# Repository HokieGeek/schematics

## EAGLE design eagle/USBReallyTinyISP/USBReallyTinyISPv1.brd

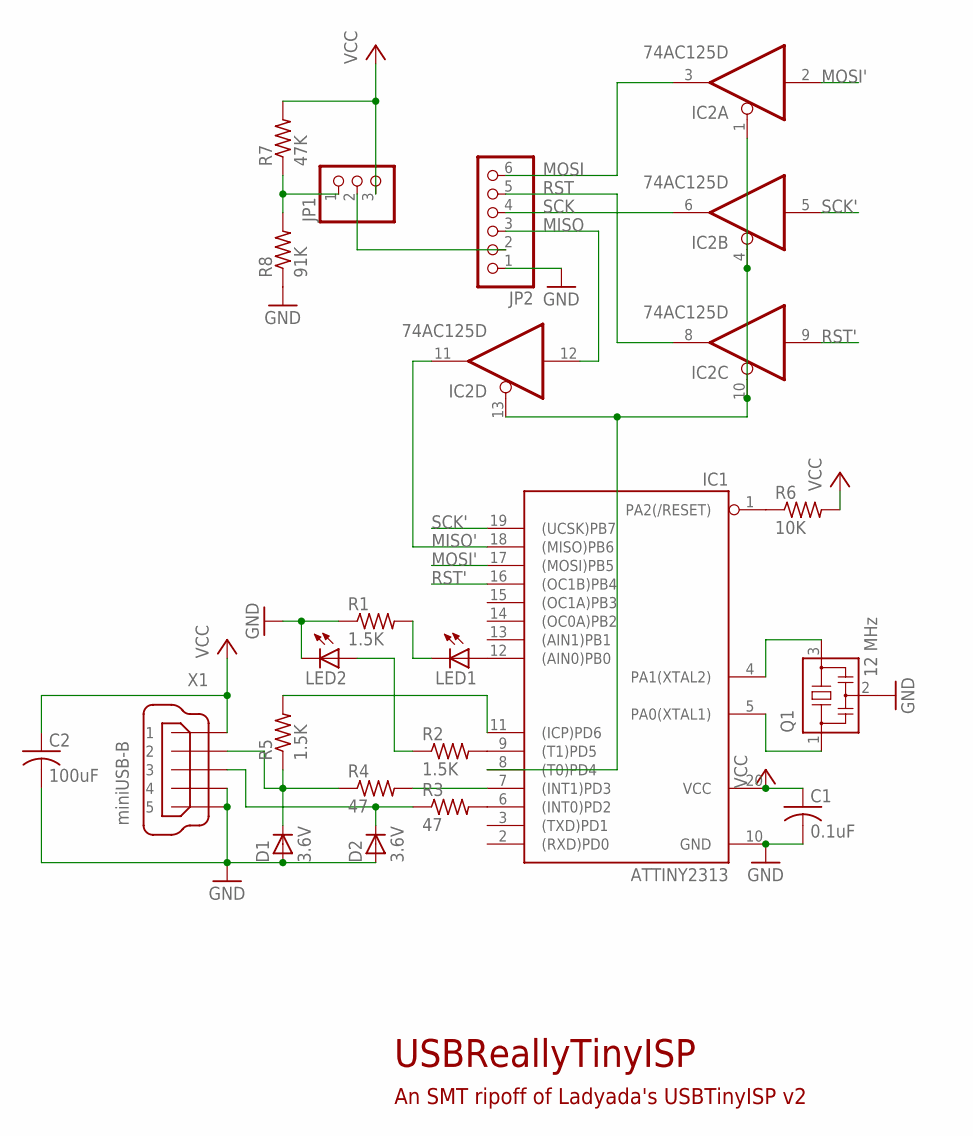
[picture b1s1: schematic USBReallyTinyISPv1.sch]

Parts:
C1: 0.1uF; C0805
C2: 100uF; C1206
D1, D2: 3.6V; SOD3718X135N
IC1: ATTINY2313; SO20L$
IC2: 74AC125D; SO14
JP1: PINHD-1X3; 1X03
JP2: PINHD-1X6; 1X06
LED1, LED2: LEDSML0805; SML0805
Q1: 12 MHz; CSTCR6M
R1, R2, R5: 1.5K; R0805
R3, R4: 47; R0805
R6: 10K; R0805
R7: 47K; R0805
R8: 91K; R0805
X1: miniUSB-B; UX60A-MB-5ST

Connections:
GND: C1.2, C2.2, D1.A, D2.A, IC1.10 (GND), IC2.7 (GND), JP2.1, LED2.C, Q1.2, R1.1, R8.1, X1.4, X1.5
MISO: IC2.12 (I), JP2.3
MISO': IC1.18 ((MISO)PB6), IC2.11 (O)
MOSI: IC2.3 (O), JP2.6
MOSI': IC1.17 ((MOSI)PB5), IC2.2 (I)
unnamed: IC1.12 ((AIN0)PB0), LED1.A
unnamed: IC1.4 (PA1(XTAL2)), Q1.3
unnamed: IC1.5 (PA0(XTAL1)), Q1.1
unnamed: IC1.1 (PA2(/RESET)), R6.1
unnamed: IC1.9 ((T1)PD5), R2.2
unnamed: LED2.A, R2.1
unnamed: LED1.C, R1.2
unnamed: IC1.6 ((INT0)PD2), R3.2
unnamed: IC1.7 ((INT1)PD3), R4.2
unnamed: D2.K, R3.1, X1.3
unnamed: D1.K, R4.1, R5.1, X1.2
unnamed: IC1.8 ((T0)PD4), IC2.1 (OE), IC2.4 (OE), IC2.10 (OE), IC2.13 (OE)
unnamed: JP1.2, JP2.2
unnamed: IC1.11 ((ICP)PD6), R5.2
unnamed: JP1.1, R7.1, R8.2
RST: IC2.8 (O), JP2.5
RST': IC1.16 ((OC1B)PB4), IC2.9 (I)
SCK: IC2.6 (O), JP2.4
SCK': IC1.19 ((UCSK)PB7), IC2.5 (I)
VCC: C1.1, C2.1, IC1.20 (VCC), IC2.14 (VCC), JP1.3, R6.2, R7.2, X1.1

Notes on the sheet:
USBReallyTinyISP
An SMT ripoff of Ladyada's USBTinyISP v2

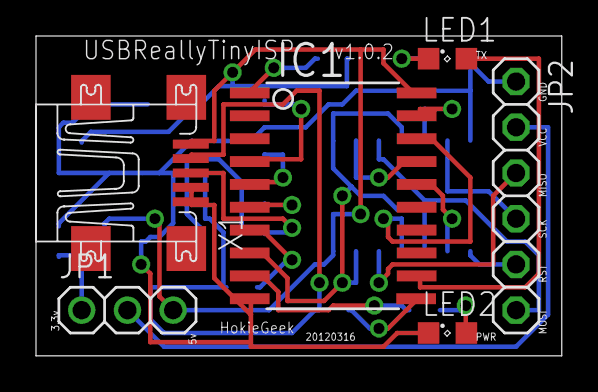
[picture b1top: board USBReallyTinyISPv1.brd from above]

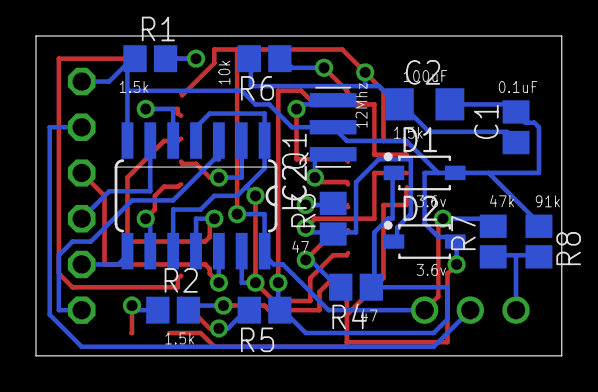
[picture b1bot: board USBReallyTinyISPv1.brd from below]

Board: 2 copper layers, 29.2 x 17.8 mm, 20 parts (14 on the bottom side), 25 nets.

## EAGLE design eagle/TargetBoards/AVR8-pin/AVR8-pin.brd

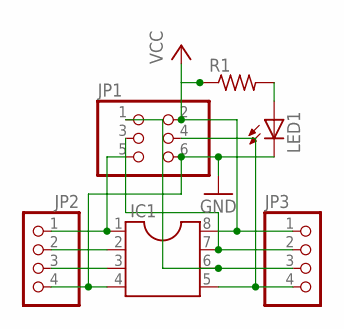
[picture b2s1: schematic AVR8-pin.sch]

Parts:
IC1: DIL8; DIL08
JP1: PINHD-2X3; 2X03
JP2, JP3: PINHD-1X4; 1X04
LED1: LED3MM
R1: R-US_0207/2V; 0207/2V

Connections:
GND: IC1.4, JP1.6, JP2.4, LED1.K (C)
unnamed: IC1.1, JP1.5, JP2.1
unnamed: LED1.A, R1.2
unnamed: IC1.7, JP1.3, JP3.2
unnamed: IC1.6, JP1.1, JP3.3
unnamed: IC1.5, JP1.4, JP3.4
unnamed: IC1.2, JP2.2
unnamed: IC1.3, JP2.3
VCC: IC1.8, JP1.2, JP3.1, R1.1

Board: 2 copper layers, 6 parts (0 on the bottom side), 9 nets, no tracks yet.

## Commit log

2013-11-15 Adding a bunch of schematics
